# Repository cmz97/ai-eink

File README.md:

# ai-eink

# System 
sudo apt-get install sysstat

# Device Tree Overlay
force_turbo=1
dtoverlay=uart3

# NFC
NFC Driver: https://github.com/2pecshy/eeprom-ST25DV-linux-driver
sudo apt install -y python3-libcamera python3-kms++ libcap-dev

# Drivers
## Camera 
sudo wget https://datasheets.raspberrypi.org/cmio/dt-blob-cam1.bin -O /boot/dt-blob.bin
libcamera-still -q 80 -o test.jpg

For OS Lite 
Open Terminal and enter "sudo nano /boot/config.txt"
Scroll down to the line that reads "camera_auto_detect=1" and change it to "camera_auto_detect=0"
On the next line, enter "dtoverlay=imx219"
Reboot

## Speakers
https://github.com/HinTak/seeed-voicecard
sudo aplay -Dhw:0 test.wav
sudo arecord -D hw:0,0 -f S32_LE -r 16000 -c 2 test.wav
https://www.waveshare.com/wiki/WM8960_Audio_HAT
sudo alsactl store

## Pi-PICO
ampy --port /dev/tty.usbmodem112401 put main.py

## Radxa
sudo apt-get install python3-dev spidev
sudo apt-get update
sudo apt-get install python3-libgpiod

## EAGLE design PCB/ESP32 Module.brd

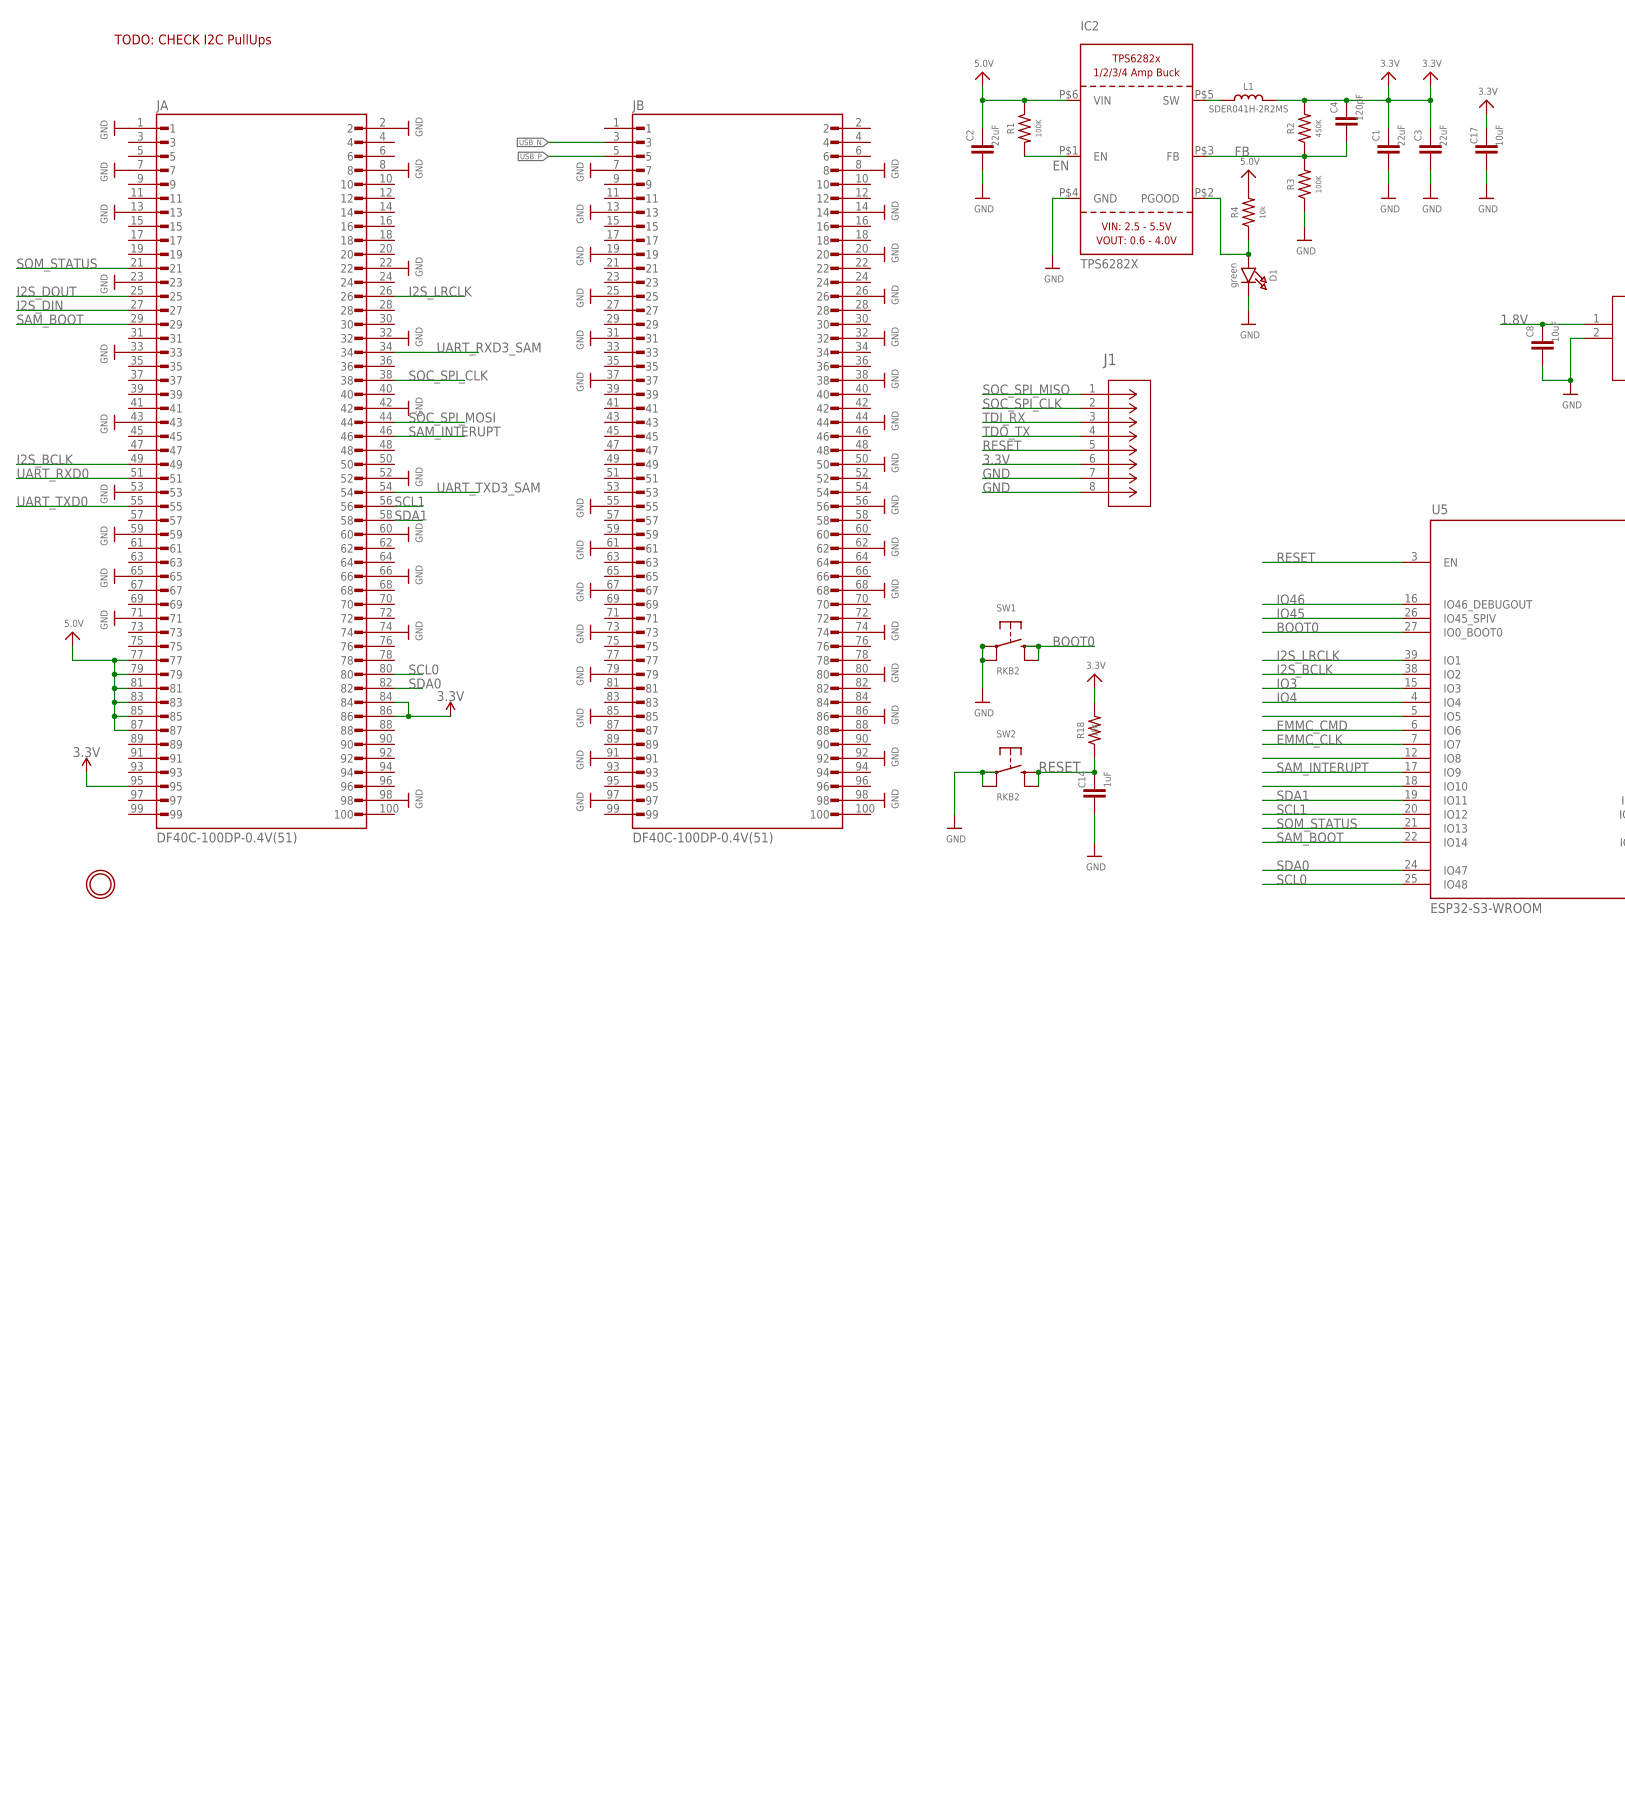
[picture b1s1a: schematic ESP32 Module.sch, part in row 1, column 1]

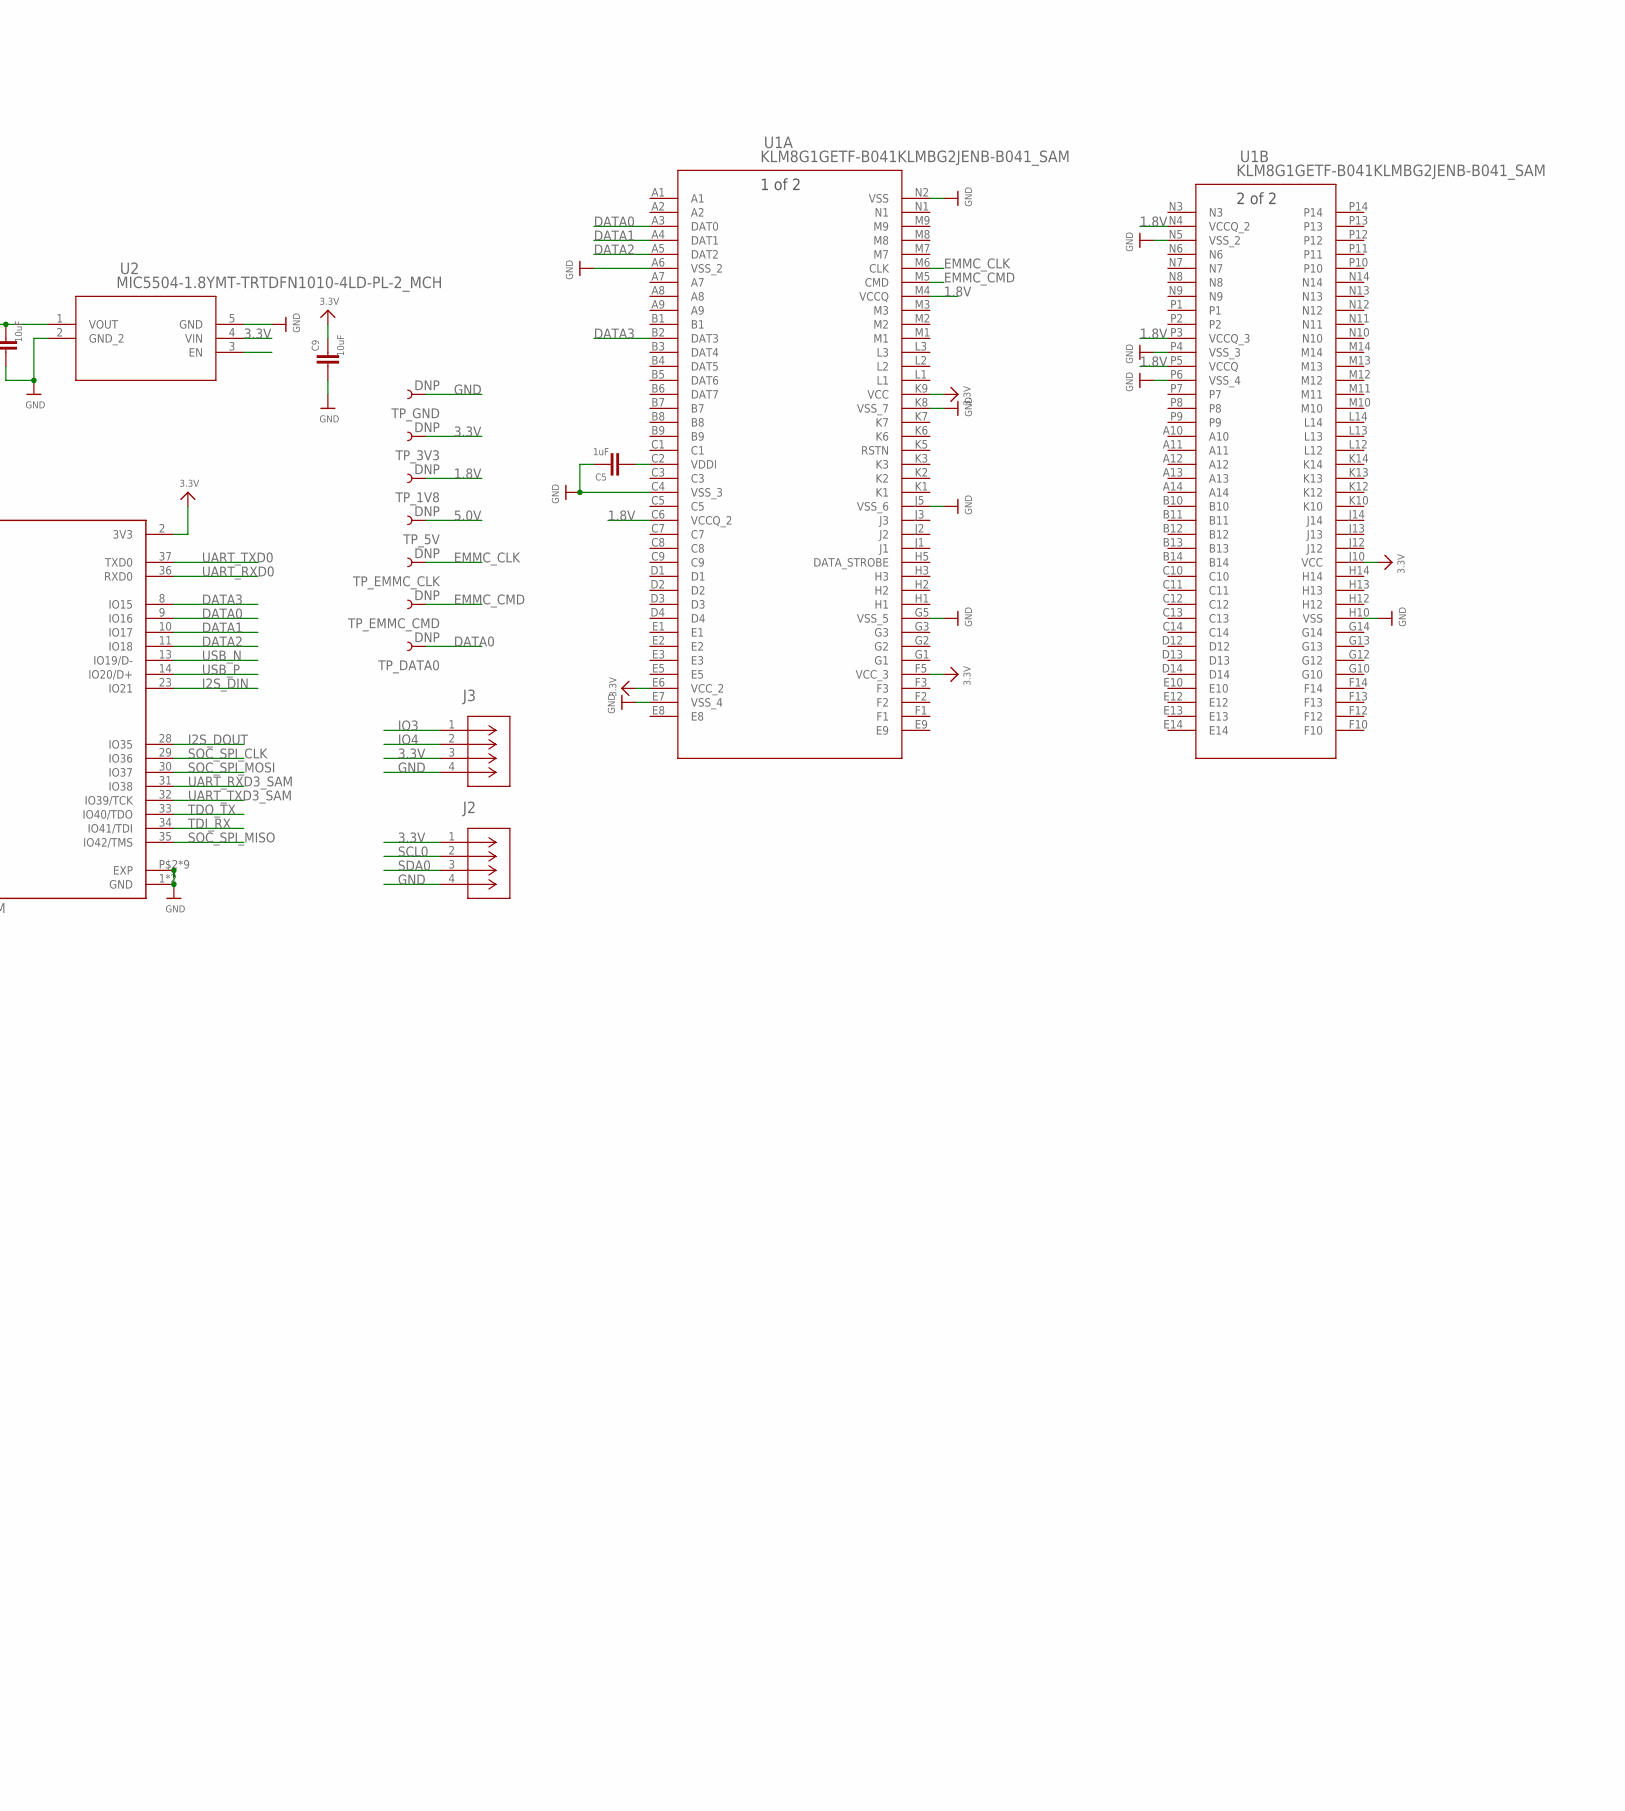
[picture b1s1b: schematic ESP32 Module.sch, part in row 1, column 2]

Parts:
C1, C3: 22uF; CAPC1005X60
C2: 22uF; CAPC1608X85
C4: 120pF; CAPC1005X60
C5, C14: 1uF; CAPC1005X60
C8, C9, C17: 10uF; CAPC1005X60
D1: green; CHIPLED_0603_NOOUTLINE
IC2: TPS6282X; VSON_6
J1: SM08B-SRSS-TB(LF)(SN)CONN_SM08B-SRSS-TB(LF)(SN)_J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; CONN_SM08B-SRSS-TB(LF)(SN)_JST
J2, J3: SM04B-SRSS-TBCONN_SM04B-SRSS-TB_JST; CONN_SM04B-SRSS-TB_JST
JA: DF40C-100DP-0.4V(51); HIROSE_DF40C-100DP-0.4V(51)
JB: DF40C-100DP-0.4V(51); HIROSE_DF40C-100DP-0.4V(51)
L1: SDER041H-2R2MS; INDUCTOR_4X4MM_SRP0415
R1, R3: 100K; RESC1005X40
R2: 450K; RESC1005X40
R4: 10k; RESC1005X40
R18: 10K; RESC1005X40
SW1, SW2: RKB2; BTN_RKB2_4.6X2.8
TP_1V8, TP_3V3, TP_5V: DNP; PAD.03X.03
TP_DATA0: DNP; PAD.03X.03
TP_EMMC_CLK: DNP; PAD.03X.03
TP_EMMC_CMD: DNP; PAD.03X.03
TP_GND: DNP; PAD.03X.03
U1: KLM8G1GETF-B041KLMBG2JENB-B041_SAM; KLMBG2JENB-B041_SAM
U2: MIC5504-1.8YMT-TRTDFN1010-4LD-PL-2_MCH; TDFN1010-4LD-PL-2_MCH
U5: ESP32-S3-WROOM; S3-WROOM32
U$2, U$120: MOUNTINGHOLE2.5; MOUNTINGHOLE_2.5_PLATED

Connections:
1.8V: C8.1, TP_1V8.P$1, U1.C6 (VCCQ_2), U1.M4 (VCCQ), U1.N4 (VCCQ_2), U1.P3 (VCCQ_3), U1.P5 (VCCQ), U2.1 (VOUT)
3.3V: C1.1, C3.1, C4.1, C9.1, C17.1, J1.6, J2.1, J3.3, JA.84, JA.86, JA.95, L1.P$2 (2), R2.2, R18.2, TP_3V3.P$1, U1.E6 (VCC_2), U1.F5 (VCC_3), U1.J10 (VCC), U1.K9 (VCC), U2.4 (VIN), U5.2 (3V3)
5.0V: C2.1, IC2.P$6 (VIN), JA.77, JA.79, JA.81, JA.83, JA.85, JA.87, R1.1, R4.2, TP_5V.P$1
BOOT0: SW1.B (S), SW1.B' (S1), U5.27 (IO0_BOOT0)
DATA0: TP_DATA0.P$1, U1.A3 (DAT0), U5.9 (IO16)
DATA1: U1.A4 (DAT1), U5.10 (IO17)
DATA2: U1.A5 (DAT2), U5.11 (IO18)
DATA3: U1.B2 (DAT3), U5.8 (IO15)
EMMC_CLK: TP_EMMC_CLK.P$1, U1.M6 (CLK), U5.7 (IO7)
EMMC_CMD: TP_EMMC_CMD.P$1, U1.M5 (CMD), U5.6 (IO6)
EN: IC2.P$1 (EN), R1.2
FB: C4.2, IC2.P$3 (FB), R2.1, R3.2
GND: C1.2, C2.2, C3.2, C5.1, C8.2, C9.2, C14.2, C17.2, D1.C, IC2.P$4 (GND), J1.7, J1.8, J2.4, J3.4, JA.1, JA.2, JA.7, JA.8, JA.13, JA.22, JA.23, JA.32, JA.33, JA.42, JA.43, JA.52, JA.53, JA.59, JA.60, JA.65, JA.66, JA.71, JA.74, JA.98, JB.7, JB.8, JB.13, JB.14, JB.19, JB.20, JB.25, JB.26, JB.31, JB.32, JB.37, JB.38, JB.44, JB.50, JB.55, JB.56, JB.61, JB.62, JB.67, JB.68, JB.73, JB.74, JB.79, JB.80, JB.85, JB.86, JB.91, JB.92, JB.97, JB.98, R3.1, SW1.A, SW1.A' (P1), SW2.A, SW2.A' (P1), TP_GND.P$1, U1.A6 (VSS_2), U1.C4 (VSS_3), U1.E7 (VSS_4), U1.G5 (VSS_5), U1.H10 (VSS), U1.J5 (VSS_6), U1.K8 (VSS_7), U1.N2 (VSS), U1.N5 (VSS_2), U1.P4 (VSS_3)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
I2S_BCLK: JA.49, U5.38 (IO2)
I2S_DIN: JA.27, U5.23 (IO21)
I2S_DOUT: JA.25, U5.28 (IO35)
I2S_LRCLK: JA.26, U5.39 (IO1)
IO3: J3.1, U5.15 (IO3)
IO4: J3.2, U5.4 (IO4)
IO10: U5.18 (IO10)
IO45: U5.26 (IO45_SPIV)
IO46: U5.16 (IO46_DEBUGOUT)
unnamed: IC2.P$5 (SW), L1.P$1 (1)
unnamed: D1.A, IC2.P$2 (PGOOD), R4.1
unnamed: C5.2, U1.C2 (VDDI)
RESET: C14.1, J1.5, R18.1, SW2.B (S), SW2.B' (S1), U5.3 (EN)
SAM_BOOT: JA.29, U5.22 (IO14)
SAM_INTERUPT: JA.46, U5.17 (IO9)
SCL0: J2.2, JA.80, U5.25 (IO48)
SCL1: JA.56, U5.20 (IO12)
SDA0: J2.3, JA.82, U5.24 (IO47)
SDA1: JA.58, U5.19 (IO11)
SOC_SPI_CLK: J1.2, JA.38, U5.29 (IO36)
SOC_SPI_MISO: J1.1, U5.35 (IO42/TMS)
SOC_SPI_MOSI: JA.44, U5.30 (IO37)
SOM_STATUS: JA.21, U5.21 (IO13)
TDI_RX: J1.3, U5.34 (IO41/TDI)
TDO_TX: J1.4, U5.33 (IO40/TDO)
UART_RXD0: JA.51, U5.36 (RXD0)
UART_RXD3_SAM: JA.34, U5.31 (IO38)
UART_TXD0: JA.55, U5.37 (TXD0)
UART_TXD3_SAM: JA.54, U5.32 (IO39/TCK)
USB_N: JB.3, U5.13 (IO19/D-)
USB_P: JB.5, U5.14 (IO20/D+)

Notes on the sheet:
TODO: CHECK I2C PullUps

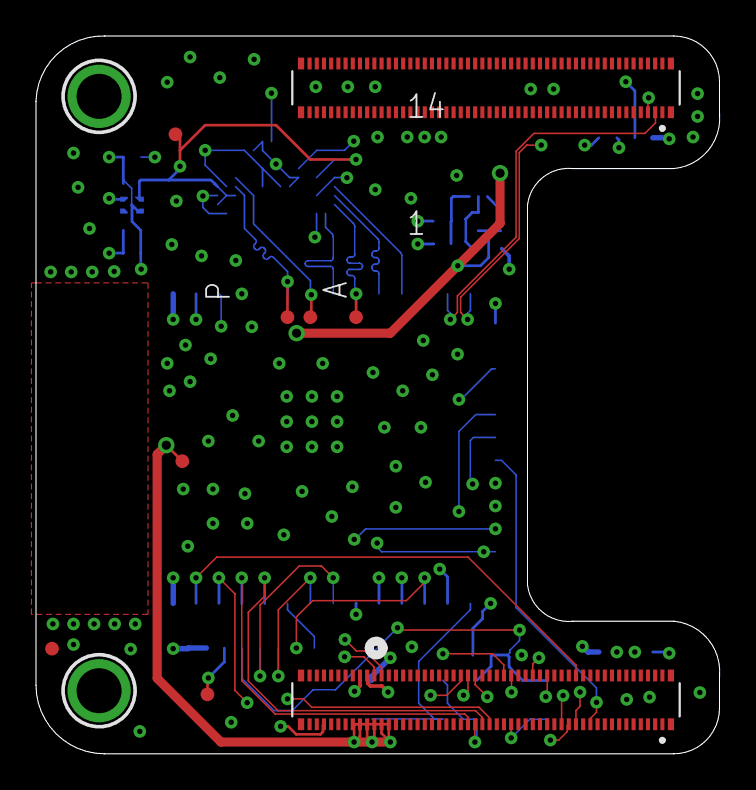
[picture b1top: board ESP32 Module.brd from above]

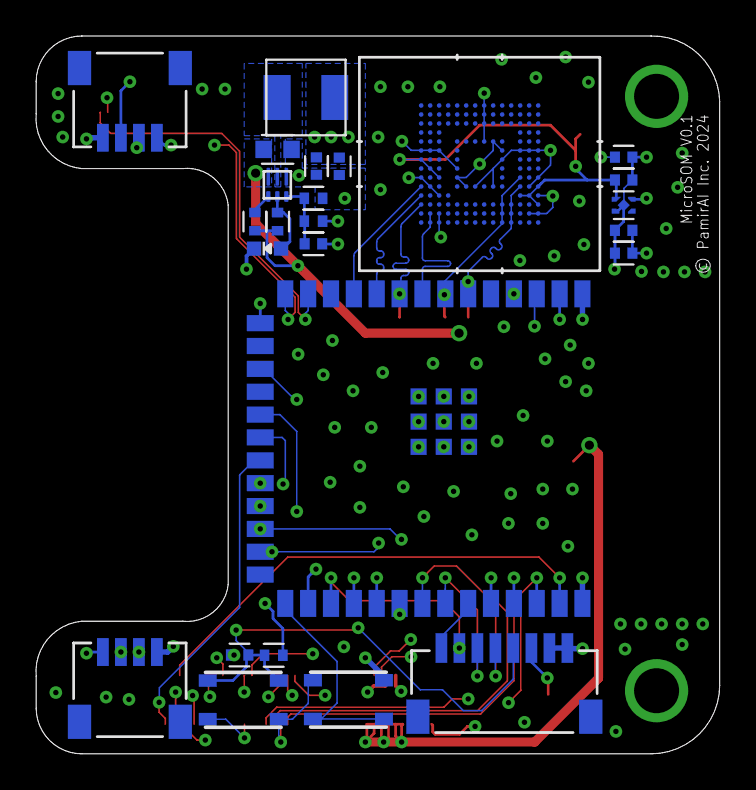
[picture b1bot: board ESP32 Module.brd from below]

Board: 4 copper layers, 38.0 x 39.9 mm, 36 parts (25 on the bottom side), 41 nets.

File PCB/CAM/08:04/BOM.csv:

Comment,Designator,Footprint,LCSC Part #
1uF,C5 C14,CAPC1005X60,
10K,R18,RESC1005X40,
10k,R4,RESC1005X40,
10uF,C8 C9 C17,CAPC1005X60,
22uF,C1,CAPC1005X60,
22uF,C2,CAPC1608X85,
22uF,C3,CAPC1005X60,
100K,R1 R3,RESC1005X40,
120pF,C4,CAPC1005X60,
450K,R2,RESC1005X40,
ESP32-S3-WROOM,U5,S3-WROOM32,
KLM8G1GETF-B041KLMBG2JENB-B041_SAM,U1,KLMBG2JENB-B041_SAM,
MIC5504-1.8YMT-TRTDFN1010-4LD-PL-2_MCH,U2,TDFN1010-4LD-PL-2_MCH,
RKB2,SW1 SW2,BTN_RKB2_4.6X2.8,
SDER041H-2R2MS,L1,INDUCTOR_4X4MM_SRP0415,
SM04B-SRSS-TBCONN_SM04B-SRSS-TB_JST,J2 J3,CONN_SM04B-SRSS-TB_JST,
SM08B-SRSS-TB(LF)(SN)CONN_SM08B-SRSS-TB(LF)(SN)_JST,J1,CONN_SM08B-SRSS-TB(LF)(SN)_JST,
TPS6282X,IC2,VSON_6,
green,D1,CHIPLED_0603_NOOUTLINE,
DF40C-100DP-0.4V(51),JA JB,HIROSE_DF40C-100DP-0.4V(51),
DNP,TP_1V8 TP_3V3 TP_5V TP_DATA0 TP_EMMC_CLK TP_EMMC_CMD TP_GND,PAD.03X.03,

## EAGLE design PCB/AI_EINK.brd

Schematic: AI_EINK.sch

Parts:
BUD: EVQ-P7A01P; SW_EVQ-P7A01P
BUP: EVQ-P7A01P; SW_EVQ-P7A01P
BUS: EVQ-P7A01P; SW_EVQ-P7A01P
C1, C3, C7, C21, C22, C23, C26, C28, C32, C33, C36, C40, C45, C46, C53, C59, C60, C61, C62, C65, C68, C79, C80: 10uF; CAPC1005X60
C2: 2.2uF; CAPC1005X60
C4, C24, C31, C43, C44, C47, C48, C49, C50, C58, C67, C69, C71, C72, C73, C74, C77: 0.1uF; CAPC1005X60
C5, C8, C9, C10, C11, C12, C13, C14, C15, C16, C34, C35: 1uF; CAPC1005X60
C6, C25: 100uF; C1210
C17: 4.7uF/50V; CAPC1005X60
C18: 4.7uF; CAPC1608X85
C19, C30, C75, C76: 1.0uF; CAPC1005X60
C20: 0.47uF; CAPC1005X60
C27: 27pF; CAPC1005X60
C29: 4.7uF; CAPC1005X60
C42: 0.1uF; CAPC1608X85
C63, C64: 100pF; CAPC1005X60
C66: 2.2uF+; CAPC1005X60
C82, C83: 15p; CAPC1005X60
C2040: RP2040TR13QFN56_7X7_RPI; QFN56_7X7_RPI
CAMERA: C262642; CON_524372271_MOL
D1: ACT (MHT192JGCT); LED-0603@1
D2, D3, D4: MBR0530; SOD3716X135N
D5: CHARGING FC-1608B1-470; LED-0603
D6, D7: PMIC; LED-0603
EINK_524352471: 524372471; CON_524372471_MOL
FB1, FB2, FB3, FB5: FERRITE_BEAD; BEADC1608X95N
GND, GND7, GND13, GND22, GND26, GND27, GND34, GND36, GND37, GND40, GND41, GND42: DNP; PAD.03X.03
H2: BM04B-SRSS-TBCONN4_BM04B-SRSS_JST; CONN4_BM04B-SRSS_JST
IC1: LIS3MDL; LGA12_2X2MM
IC3: WM8960; QFN32_5MM
J1: SM03B-SRSS-TBCONN_SM03B-SRSS-TB_JST; CONN_SM03B-SRSS-TB_JST
J2: C393939; USB-C-16P
J4, J5: BM04B-SRSS-TBCONN4_BM04B-SRSS_JST; CONN4_BM04B-SRSS_JST
J6: SM04B-SRSS-TBCONN_SM04B-SRSS-TB_JST; CONN_SM04B-SRSS-TB_JST
L1: 6.8uH C36410; INDUCTOR_5X5MM_TDK_VLC5045
L3: FNR5012S100MT 10uH; IND_LQH5BPN2R2NT0L
LED2: LED_RED; LEDC1608X65N_RND-R
LED3: SYS_POW (19-213/Y2C-CQ2R2L/3T(CY)); LED-0603
LOW_BATT: LED_RED; LEDC1608X65N_RND-R
LS1: CMS-18138A-SP; CUI_CMS-18138A-SP
M.2KEYM(NGFF): 1-2199119-5 OR C841645; TE_1-2199119-5
OSC2: ECS-3225MV; OSC_3.2X2.5MM
Q1: SI1308EDL-T1-GE3; SOT65P210X110-3N
Q2: DMG2307L; SOT96P240X110-3N
Q3, Q4: NMOS_C7465427; SOT23
R1: 1.87M (TPA2005D1DRBR); RESC1005X40
R2: 340K (RTT053403FTP); RESC1005X40
R3: 1.87M; RESC1005X40
R4, R13, R36: 200K; RESC1005X40
R5, R14, R20, R23: 1K; RESC1005X40
R6: 590; RESC1005X40
R7: 1.1k; RESC1005X40
R8, R10, R34, R35: 1k; RESC1005X40
R9: 0.47; RESC1005X40
R11, R33, R43: 10K; RESC1005X40
R12: 0.01; 1206
R15, R18, R25, R26, R40, R42: 4.7K; RESC1005X40
R16, R17, R27, R28, R37, R39: 10k; RESC1005X40
R19: 5.1K; RESC1005X40
R21: 5.1k; RESC1005X40
R22: 180; RESC1005X40
R24: 100k; RESC1005X40
R30: 36k; RESC1005X40
R31, R32: 27; RESC1005X40
R38: 4.7k; RESC1005X40
R41: 47K; RESC1005X40
R44: 6.57k; RESC1005X40
RPI-CM1: DF40C-100DS-0.4V(51); RPI-CM4
RPIBOOT, RPIBOOT1, RPIBOOT2, RPIBOOT3, RPIBOOT4, RPIBOOT6, RPIBOOT8, RPIBOOT9, RPIBOOT10, RPIBOOT11, RPIBOOT12: DNP; PAD.03X.03
RPIBOOT5, RPIBOOT7: TEST-POINT3; PAD.03X.03
SJ1, SJ6: DNP; PAD-JUMPER-2-NC_BY_TRACE_YES_SILK
T1: MMUN2133LT1G; SC59-BEC
U1: TPS61092RSAR; PVQFN-16
U2: MC74VHC1G14DFT1G; SOT65P210X110-5N
U3: BQ27441DRZR-G1A; PDSO-N12
U4: BQ24075; PVQFN-N16
U5: MC74VHC1G14DFT1G OR C66196; SOT65P210X110-5N
U6: LSM6DS3; LGA-14L
U7: SN74LVC244ARWPRRWP0020A; RWP0020A
U9: EMC2301-1-ACZL-TRMSOP8_MC_MCH-L; MSOP8_MC_MCH-L
U10, U11, U15: AP2112-3.3K; SOT23-5
U12: C233266; XDCR_SPU0410LR5H-QB
U13: TPD4EUSB30DQARDQA10; DQA10
U14: OPA344; SOT23-5
U16: W25Q16JVUXIQ_TR; PSON50P300X200X60-9N
U17, U18, U19, U20, U21, U22, U23, U24: TPD1E1B04DPYRDPY2_TEX; DPY2_TEX
U25: DRV2605LDGSR; SOP50P490X110-10N
USB2.0MUX: TS3USB30RSWR; 10-UFQFN
USB_BOOT_N: DNP; PAD.03X.03
Y1: ABM8-272-T3; ABM8272T3

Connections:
1V8BQ: C20.1, U3.5 (VDD)
2A3: U7.14 (2A3)
2A4: U7.16 (2A4)
2Y3: U7.4 (2Y3)
2Y4: U7.2 (2Y4)
3.3V: C28.1, C36.2, C49.1, CAMERA.22, D1.A, IC1.5 (VDD), IC1.6 (VDDIO), IC3.8 (DCVDD), IC3.10 (DBVDD), OSC2.1 (INH), OSC2.4 (VCC), R15.2, R18.2, R30.2, R33.2, RPI-CM1.84 (CM4_3.3V(OUTPUT)), RPI-CM1.86 (CM4_3.3V(OUTPUT)), RPIBOOT2.P$1, SJ6.1, U2.5 (VCC), U6.5 (VDDIO), U6.8 (VDD), U9.3 (VDD)
3V3_EINK: C9.1, C17.1, EINK_524352471.9, EINK_524352471.10, L3.1, Q2.3 (D)
5.0V: C2.1, C6.1, C25.1, C42.1, C59.1, C60.1, C61.1, C65.1, C66.1, IC3.21 (SPKVDD2), IC3.26 (SPKVDD1), J6.3, R3.2, R5.1, RPI-CM1.77 (+5V(INPUT)), RPI-CM1.79 (+5V(INPUT)), RPI-CM1.81 (+5V(INPUT)), RPI-CM1.83 (+5V(INPUT)), RPI-CM1.85 (+5V(INPUT)), RPI-CM1.87 (+5V(INPUT)), RPIBOOT1.P$1, U1.1 (VOUT), U1.15 (VOUT), U1.16 (VOUT), U10.1 (IN), U10.3 (EN)
!CE!: R24.1, U4.4 (!CE!)
!CHG!: R22.2, U4.9 (!CHG!)
AGND: C67.2, C68.2, FB5.2, IC3.28 (AGND), IC3.33 (AGND)
AUDIO_MCLK: IC3.11 (MCLK), OSC2.3 (OUT)
AVDD: C50.1, C58.1, C67.1, C68.1, FB1.2, IC3.32 (AVDD), R27.2, U12.4 (VDD), U14.5 (P$V+)
BATTERY_IN: C19.1, J1.3, R12.2, U3.6 (BAT), U3.8 (SRP)
BOOST_EN: Q3.3 (D), R13.1, R36.2
BUTTON_D: BUD.2_1 (2), BUD.2_2 (2), C2040.29 (GPIO18)
BUTTON_S: BUS.2_1 (2), BUS.2_2 (2), C2040.27 (GPIO16)
BUTTON_U: BUP.2_1 (2), BUP.2_2 (2), C2040.28 (GPIO17)
CAM0_C_N: RPI-CM1.140 (CAM0_C_N)
CAM0_C_P: RPI-CM1.142 (CAM0_C_P)
CAM0_D0_N: RPI-CM1.128 (CAM0_D0_N)
CAM0_D0_P: RPI-CM1.130 (CAM0_D0_P)
CAM0_D1_N: RPI-CM1.134 (CAM0_D1_N)
CAM0_D1_P: RPI-CM1.136 (CAM0_D1_P)
CAM1_C_N: CAMERA.8, RPI-CM1.127 (CAM1_C_N)
CAM1_C_P: CAMERA.9, RPI-CM1.129 (CAM1_C_P)
CAM1_D0_N: CAMERA.2, RPI-CM1.115 (CAM1_D0_N)
CAM1_D0_P: CAMERA.3, RPI-CM1.117 (CAM1_D0_P)
CAM1_D1_N: CAMERA.5, RPI-CM1.121 (CAM1_D1_N)
CAM1_D1_P: CAMERA.6, RPI-CM1.123 (CAM1_D1_P)
CAM1_D2_N: CAMERA.11, RPI-CM1.133 (CAM1_D2_N)
CAM1_D2_P: CAMERA.12, RPI-CM1.135 (CAM1_D2_P)
CAM1_D3_N: CAMERA.14, RPI-CM1.139 (CAM1_D3_N)
CAM1_D3_P: CAMERA.15, RPI-CM1.141 (CAM1_D3_P)
CAM_GPIO: CAMERA.17, RPI-CM1.97 (CAMERA_GPIO)
CDD: C10.1, EINK_524352471.7
DSI0_C_N: RPI-CM1.169 (DSI0_C_N)
DSI0_C_P: RPI-CM1.171 (DSI0_C_P)
DSI0_D0_N: RPI-CM1.157 (DSI0_D0_N)
DSI0_D0_P: RPI-CM1.159 (DSI0_D0_P)
DSI0_D1_N: RPI-CM1.163 (DSI0_D1_N)
DSI0_D1_P: RPI-CM1.165 (DSI0_D1_P)
DSI1_C_N: RPI-CM1.187 (DSI1_C_N)
DSI1_C_P: RPI-CM1.189 (DSI1_C_P)
DSI1_D0_N: RPI-CM1.175 (DSI1_D0_N)
DSI1_D0_P: RPI-CM1.177 (DSI1_D0_P)
DSI1_D1_N: RPI-CM1.181 (DSI1_D1_N)
DSI1_D1_P: RPI-CM1.183 (DSI1_D1_P)
DSI1_D2_N: RPI-CM1.193 (DSI1_D2_N)
DSI1_D2_P: RPI-CM1.195 (DSI1_D2_P)
DSI1_D3_N: RPI-CM1.194 (DSI1_D3_N)
DSI1_D3_P: RPI-CM1.196 (DSI1_D3_P)
EINK_BUSY: C2040.13 (GPIO10), EINK_524352471.16, RPIBOOT9.P$1, U7.1 (1A1), U18.2 (I/O)
EINK_CS: C2040.16 (GPIO13), EINK_524352471.13, GND41.P$1, U7.11 (1Y4), U20.2 (I/O)
EINK_D/C: C2040.15 (GPIO12), EINK_524352471.14, RPIBOOT10.P$1, U7.13 (1Y3), U19.2 (I/O)
EINK_RESET: C2040.14 (GPIO11), EINK_524352471.15, GND40.P$1, U7.15 (1Y2), U17.2 (I/O)
ENABLE: R13.2, U1.11 (EN)
EXT_VCC_PCIE: M.2KEYM(NGFF).2, M.2KEYM(NGFF).4, M.2KEYM(NGFF).12, M.2KEYM(NGFF).14, M.2KEYM(NGFF).16, M.2KEYM(NGFF).18, M.2KEYM(NGFF).70, M.2KEYM(NGFF).72, M.2KEYM(NGFF).74, RPIBOOT3.P$1
FAN_PWM: J6.1, U9.5 (PWM)
GDR: EINK_524352471.23, Q1.1 (G), R11.2
GND: C1.2, C2.2, C3.2, C4.2, C5.2, C6.2, C7.2, C8.2, C9.2, C10.2, C11.2, C12.2, C13.2, C14.2, C15.2, C16.2, C17.2, C19.2, C20.2, C21.2, C22.2, C23.2, C24.1, C25.2, C26.2, C28.2, C30.2, C31.2, C32.2, C33.2, C34.1, C35.2, C36.1, C40.2, C42.2, C43.2, C44.2, C45.2, C46.2, C47.2, C48.2, C49.2, C50.2, C53.2, C58.2, C59.2, C60.2, C61.2, C62.2, C63.2, C64.2, C65.2, C66.2, C69.2, C71.2, C72.2, C73.2, C74.2, C75.2, C76.2, C77.2, C79.2, C80.2, C82.2, C83.1, C2040.19 (TESTEN), C2040.57 (GND), CAMERA.1, CAMERA.4, CAMERA.7, CAMERA.10, CAMERA.13, CAMERA.16, CAMERA.19, CAMERA.P1, CAMERA.P2, D2.1 (K), EINK_524352471.8, EINK_524352471.17, EINK_524352471.P1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
GND_2: U13.3 (GND_2)
GPOUT: R33.1, U3.12 (GPOUT)
HAP_3V3: C33.1, C35.1, U15.5 (OUT), U25.5 (EN), U25.6 (VDD/NC), U25.10 (VDD)
HDMI0_CEC: RPI-CM1.151 (HDMI0_CEC)
HDMI0_CLK_N: RPI-CM1.190 (HDMI0_CLK_N)
HDMI0_CLK_P: RPI-CM1.188 (HDMI0_CLK_P)
HDMI0_HOTPLUG: RPI-CM1.153 (HDMI0_HOTPLUG)
HDMI0_SCL: RPI-CM1.200 (HDMI0_SCL)
HDMI0_SDA: RPI-CM1.199 (HDMI0_SDA)
HDMI0_TX0_N: RPI-CM1.184 (HDMI0_TX0_N)
HDMI0_TX0_P: RPI-CM1.182 (HDMI0_TX0_P)
HDMI0_TX1_N: RPI-CM1.178 (HDMI0_TX1_N)
HDMI0_TX1_P: RPI-CM1.176 (HDMI0_TX1_P)
HDMI0_TX2_N: RPI-CM1.172 (HDMI0_TX2_N)
HDMI0_TX2_P: RPI-CM1.170 (HDMI0_TX2_P)
HDMI1_CEC: RPI-CM1.149 (HDMI1_CEC)
HDMI1_CLK_N: RPI-CM1.166 (HDMI1_CLK_N)
HDMI1_CLK_P: RPI-CM1.164 (HDMI1_CLK_P)
HDMI1_HOTPLUG: RPI-CM1.143 (HDMI1_HOTPLUG)
HDMI1_SCL: RPI-CM1.147 (HDMI1_SCL)
HDMI1_SDA: RPI-CM1.145 (HDMI1_SDA)
HDMI1_TX0_N: RPI-CM1.160 (HDMI1_TX0_N)
HDMI1_TX0_P: RPI-CM1.158 (HDMI1_TX0_P)
HDMI1_TX1_N: RPI-CM1.154 (HDMI1_TX1_N)
HDMI1_TX1_P: RPI-CM1.152 (HDMI1_TX1_P)
HDMI1_TX2_N: RPI-CM1.148 (HDMI1_TX2_N)
HDMI1_TX2_P: RPI-CM1.146 (HDMI1_TX2_P)
I2S_BCLK: IC3.12 (BCLK), RPI-CM1.49 (GPIO18)
I2S_DIN: IC3.16 (ADCDAT), RPI-CM1.27 (GPIO20)
I2S_DOUT: IC3.14 (DACDAT), RPI-CM1.25 (GPIO21)
I2S_LRCLK: IC3.13 (DACLRC), IC3.15 (ADCLRC/GPIO1), RPI-CM1.26 (GPIO19)
ILIM: R7.1, U4.12 (ILIM)
ISET: R6.1, U4.16 (ISET)
LBO: T1.B, U1.12 (LBO)
LEFT_N: C64.1, FB3.2, LS1.N
LEFT_P: C63.1, FB2.2, LS1.P
MICBIAS: C46.1, C48.1, IC3.1 (MICBIAS)
unnamed: L1.P$2 (2), U1.3 (SW), U1.4 (SW)
unnamed: LOW_BATT.A, R20.1
unnamed: R1.1, R2.2, U1.9 (LBI)
unnamed: LED2.A, R5.2
unnamed: R3.1, R4.2, U1.14 (FB)
unnamed: R20.2, T1.C
unnamed: RPI-CM1.78 (GPIO_VREF), SJ6.2
unnamed: C31.1, IC1.4 (C1)
unnamed: RPI-CM1.95 (PI_LED_!PWR), U2.2 (IN_A)
unnamed: C29.1, U12.1 (OUTPUT)
unnamed: R8.2, U2.4 (OUT_~Y)
unnamed: LED3.A, R8.1
unnamed: C27.1, R38.1, R39.2, U14.4 (-IN)
unnamed: R10.2, RPI-CM1.21 (PI_!LED_ACTIVITY)
unnamed: D1.C, R10.1
unnamed: C34.2, U25.1 (REG)
unnamed: D5.C, R22.1
unnamed: D7.C, R14.1
unnamed: C18.1, D2.2 (A), D3.1 (K)
unnamed: C29.2, R38.2
unnamed: D6.C, R23.1
unnamed: C30.1, R27.1, R37.2, U14.3 (+IN)
unnamed: C18.2, D4.2 (A), L3.2, Q1.3 (D)
unnamed: Q4.3 (D), R34.2, USB_BOOT_N.P$1
unnamed: C83.2, R35.2, Y1.3 (CRYSTAL_2)
unnamed: J2.B5 (CC2), R21.2
unnamed: Q2.1 (G), R43.2, R44.1
unnamed: R44.2, U5.4 (OUT_~Y)
unnamed: J2.A5 (CC1), R19.2
unnamed: FB2.1, IC3.25 (SPK_LP)
unnamed: FB3.1, IC3.23 (SPK_LN)
NC: EINK_524352471.24
N_RPIBOOT: RPI-CM1.93 (!RPIBOOT), RPIBOOT.P$1
OUT: C62.1, C69.1, FB1.1, U10.5 (OUT)
PCIE_!RST: M.2KEYM(NGFF).50, RPI-CM1.109 (PCIE_!RST)
PCIE_CLK_!REQ: M.2KEYM(NGFF).52, RPI-CM1.102 (PCIE_CLK_!REQ)
PCIE_CLK_N: M.2KEYM(NGFF).53, RPI-CM1.112 (PCIE_CLK_N)
PCIE_CLK_P: M.2KEYM(NGFF).55, RPI-CM1.110 (PCIE_CLK_P)
PCIE_RX_N: M.2KEYM(NGFF).41, RPI-CM1.118 (PCIE_RX_N)
PCIE_RX_P: M.2KEYM(NGFF).43, RPI-CM1.116 (PCIE_RX_P)
PCIE_TX_N: M.2KEYM(NGFF).47, RPI-CM1.124 (PCIE_TX_N)
PCIE_TX_P: M.2KEYM(NGFF).49, RPI-CM1.122 (PCIE_TX_P)
PI_1V8: RPI-CM1.88 (CM4_1.8V(OUTPUT)), RPI-CM1.90 (CM4_1.8V(OUTPUT))
PREVGH: C16.1, D4.1 (K), EINK_524352471.4
PREVGL: C14.1, D3.2 (A), EINK_524352471.2
RESE: EINK_524352471.22, Q1.2 (S), R9.2
RESERVED@104: RPI-CM1.104 (RESERVED)
RESERVED@106: RPI-CM1.106 (RESERVED)
RINPUT1: C27.2, IC3.5 (RINPUT1), R39.1, U14.1 (OUT)
SAM_1V1: C76.1, C77.1, C2040.23 (DVDD_2), C2040.45 (VREG_VOUT), C2040.50 (DVDD)
SAM_3V3: BUD.1_1 (1), BUD.1_2 (1), BUP.1_1 (1), BUP.1_2 (1), BUS.1_1 (1), BUS.1_2 (1), C7.1, C24.2, C43.1, C44.1, C71.1, C72.1, C73.1, C74.1, C75.1, C80.1, C2040.1 (IOVDD_2), C2040.10 (IOVDD_3), C2040.22 (IOVDD_4), C2040.33 (IOVDD_5), C2040.42 (IOVDD_6), C2040.43 (ADC_AVDD), C2040.44 (VREG_VIN), C2040.48 (USB_VDD), C2040.49 (IOVDD), D7.A, J4.1, Q2.2 (S), R16.2, R17.2, R25.2, R26.2, R28.2, R40.2, R42.2, R43.1, U5.5 (VCC), U7.19 (VCC), U11.5 (OUT), U16.8 (VCC), USB2.0MUX.9 (VCC)
SAM_BOOT: Q4.1 (G), RPI-CM1.29 (GPIO16)
SAM_EINK_PWR: C2040.12 (GPIO9), U5.2 (IN_A)
SAM_EINK_SWITCH: C2040.34 (GPIO22), U7.18 (2OE_N), U7.20 (1OE_N)
SAM_GPIO3: C2040.5 (GPIO3)
SAM_GPIO4: C2040.6 (GPIO4)
SAM_GPIO5: C2040.7 (GPIO5)
SAM_GPIO6: C2040.8 (GPIO6)
SAM_GPIO7: C2040.9 (GPIO7)
SAM_GPIO8: C2040.11 (GPIO8)
SAM_GPIO23: C2040.35 (GPIO23)
SAM_GPIO26/ADC0: C2040.38 (GPIO26/ADC0)
SAM_GPIO27/ADC1: C2040.39 (GPIO27/ADC1)
SAM_GPIO28/ADC2: C2040.40 (GPIO28/ADC2)
SAM_GPIO29/ADC3: C2040.41 (GPIO29/ADC3)
SAM_INTERUPT: C2040.4 (GPIO2), RPI-CM1.46 (GPIO22), RPIBOOT12.P$1
SAM_QSPI_SCLK: C2040.52 (QSPI_SCLK), U16.6 (CLK)
SAM_QSPI_SCN: C2040.56 (QSPI_SCN), R34.1, U16.1 (!CS!)
SAM_QSPI_SD0: C2040.53 (QSPI_SD0), U16.5 (IO0)
SAM_QSPI_SD1: C2040.55 (QSPI_SD1), U16.2 (IO1)
SAM_QSPI_SD2: C2040.54 (QSPI_SD2), U16.3 (IO2)
SAM_QSPI_SD3: C2040.51 (QSPI_SD3), U16.7 (IO3)
SAM_RUN: C2040.26 (RUN)
SAM_SCL: C2040.37 (GPIO25), J4.3, R26.1, RPIBOOT8.P$1, U3.2 (SCL), U25.2 (SCL)
SAM_SDA: C2040.36 (GPIO24), GND37.P$1, J4.2, R25.1, U3.1 (SDA), U25.3 (SDA)
SAM_SWCLK: C2040.24 (SWCLK)
SAM_SWD: C2040.25 (SWD)
SAM_USB_DM: C2040.46 (USB_DM), R32.2
SAM_USB_DP: C2040.47 (USB_DP), R31.2
SAM_USB_SWITCH: C2040.30 (GPIO19), R41.1, USB2.0MUX.8 (~OE)
SAM_XIN: C82.1, C2040.20 (XIN), Y1.1 (CRYSTAL_1)
SAM_XOUT: C2040.21 (XOUT), R35.1
SCL0: CAMERA.20, RPI-CM1.80 (SCL0)
SCL1: IC1.1 (SCL), IC3.17 (SCL), R18.1, RPI-CM1.56 (GPIO3), RPIBOOT6.P$1, U6.13 (SCL), U9.2 (SMCLK)
SDA0: CAMERA.21, RPI-CM1.82 (SDA0)
SDA1: GND7.P$1, IC1.11 (SDA), IC3.18 (SDA), R15.1, RPI-CM1.58 (GPIO2), U6.14 (SDA), U9.1 (SMDATA)
SOC_EINK_BUSY: RPI-CM1.40 (GPIO9), U7.17 (1Y1)
SOC_EINK_CS: RPI-CM1.39 (GPIO8), U7.7 (1A4)
SOC_EINK_D/C: RPI-CM1.30 (GPIO6), U7.5 (1A3)
SOC_EINK_RESET: RPI-CM1.28 (GPIO13), U7.3 (1A2)
SOC_SPI_CLK: RPI-CM1.38 (GPIO11), U7.10 (2A1)
SOC_SPI_MOSI: RPI-CM1.44 (GPIO10), U7.12 (2A2)
SPI_CLK: C2040.17 (GPIO14), EINK_524352471.12, RPIBOOT11.P$1, U7.8 (2Y1), U21.2 (I/O)
SPI_MOSI: C2040.18 (GPIO15), EINK_524352471.11, GND42.P$1, U7.6 (2Y2), U22.2 (I/O)
SYS_PI_ON: C2040.32 (GPIO21), Q3.1 (G)
TACH: J6.2, R30.1, U9.6 (TACH)
THERM: J1.2, SJ1.1
TS: SJ1.2, U3.10 (BIN), U4.1 (TS)
TSCL: EINK_524352471.19, U23.2 (I/O)
TSDA: EINK_524352471.18, U24.2 (I/O)
U25_OUT+: H2.1, H2.2, U25.7 (OUT+)
U25_OUT-: H2.3, H2.4, U25.9 (OUT-)
UART_RXD0: J5.2, RPI-CM1.51 (GPIO15)
UART_RXD3_SAM: C2040.2 (GPIO0), R40.1, RPI-CM1.34 (GPIO5), RPIBOOT7.P$1
UART_TXD0: J5.1, RPI-CM1.55 (GPIO14)
UART_TXD3_SAM: C2040.3 (GPIO1), GND36.P$1, R42.1, RPI-CM1.54 (GPIO4)
USB_N: J2.A7 (D-), J2.B7 (D-), RPI-CM1.103 (USB_N), U13.5 (D2-), USB2.0MUX.5 (D-)
USB_OTG_ID: RPI-CM1.101 (USB_OTG_ID)
USB_P: J2.A6 (D+), J2.B6 (D+), RPI-CM1.105 (USB_P), U13.4 (D2+), USB2.0MUX.3 (D+)
USB_SAM_N: R32.1, USB2.0MUX.7 (D1-)
USB_SAM_P: R31.1, USB2.0MUX.1 (D1+)
VBUS: C3.1, C22.1, C53.1, J2.VBUS1 (VBUS), J2.VBUS2 (VBUS), U4.13 (IN)
VCOM: C15.1, EINK_524352471.1
VDAC_COMP: RPI-CM1.111 (VDAC_COMP)
VGH: C8.1, EINK_524352471.20
VGL: C5.1, EINK_524352471.21
VMID: C45.1, C47.1, IC3.27 (VMID)
VOUT: C1.1, C4.1, C21.1, C26.1, C32.1, C79.1, D5.A, D6.A, L1.P$1 (1), R1.2, R36.1, RPIBOOT4.P$1, T1.E, U1.8 (VBAT), U4.5 (EN2), U4.10 (OUT), U4.11 (OUT), U11.1 (IN), U11.3 (EN), U15.1 (IN), U15.3 (EN)
VPP: C11.1, EINK_524352471.6
VSH: C12.1, EINK_524352471.5
VSL: C13.1, EINK_524352471.3
V_BATT: C23.1, C40.1, R12.1, RPIBOOT5.P$1, U3.7 (SRN), U4.2 (BAT), U4.3 (BAT)

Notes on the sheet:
Both grounds must be connected on the PCB at only one point close to the GND pin.
See Pg 15 1st para
6.8uH power w/2A current
R3 = 1.9Mohm for 5.2V R3 = 1.1Mohm for 3.3V
Sets fast charge current - R_ISET range: 590-8.9k - I_CHG = ~885 / R_ISET - EX: R_ISET = 590 : I_CHG = 1.5A
Sets combined system load and battery charge currents pulled from USB input. - I_INMAX=1650 / R_ILIM - R_ILIM range: 1.1k-8k - EX: R_ILIM = 1.1k : I_INMAX = 1.5A
BQ24075 - 1.5A USB-Friendly LiPo Battery Charger & Power-Path Management
BQ27441-G1 Fuel Gauge
SJ1: Cut to disable TS bypass.
SJ3: Cut to set custom ISET.
SJ4: Cut to set custom ILIM.
ILIM - System/Load Current Limit
ISET-Charge Current
TMR - Saftey Timers
Sets pre-charge and fast-charge safety timers. - Leave unconnected to set default (30min pre, 5hr charge time) - Connect to GND to disable - R_TMR range: 18k-72k - T_PRE range: 1400-2160 s - T_PRE (s) = 0.048 * R_TMR - T_MAX (s) = 10 * T_PRE
SJ2: Cut to enable charge timer.
TS - External Thermistor
- Connect TS to 10k NTC thermistor in the battery pack. - Connect a 10k resistor to GND if TS is not used.
VDD is 1.8V generated internally
OUT is the power-path management output. It manages current supplied from the USB input to both the battery and system. Or supplies battery power to the system when USB is not connected. OUT supply w/ USB: V_USB - 0.3V OUT supply w/o USB: V_BAT - 0.05V
I2C ADDR: 0x55
SJ5 sets the operation of the power LED. To either: - Power OUT indicator - !PGOOD! indicator (Good IN supply) - Open (LED disconnected)
5V BOOST
OE HIGH = Disconnected OE LOW = Connected S LOW = D1 S HIGH = D2
MOTION SUBSYSTEM
AUDIO SUBSYSTEM
POWER SUBSYSTEM
SOM
EINK_SUBSYSTEM
SAM
USB2.0
HAPTIC MOTOR
ACTIVE COOLING
DIGITAL PERIPHERAL
PCIE M.2
CAMERA

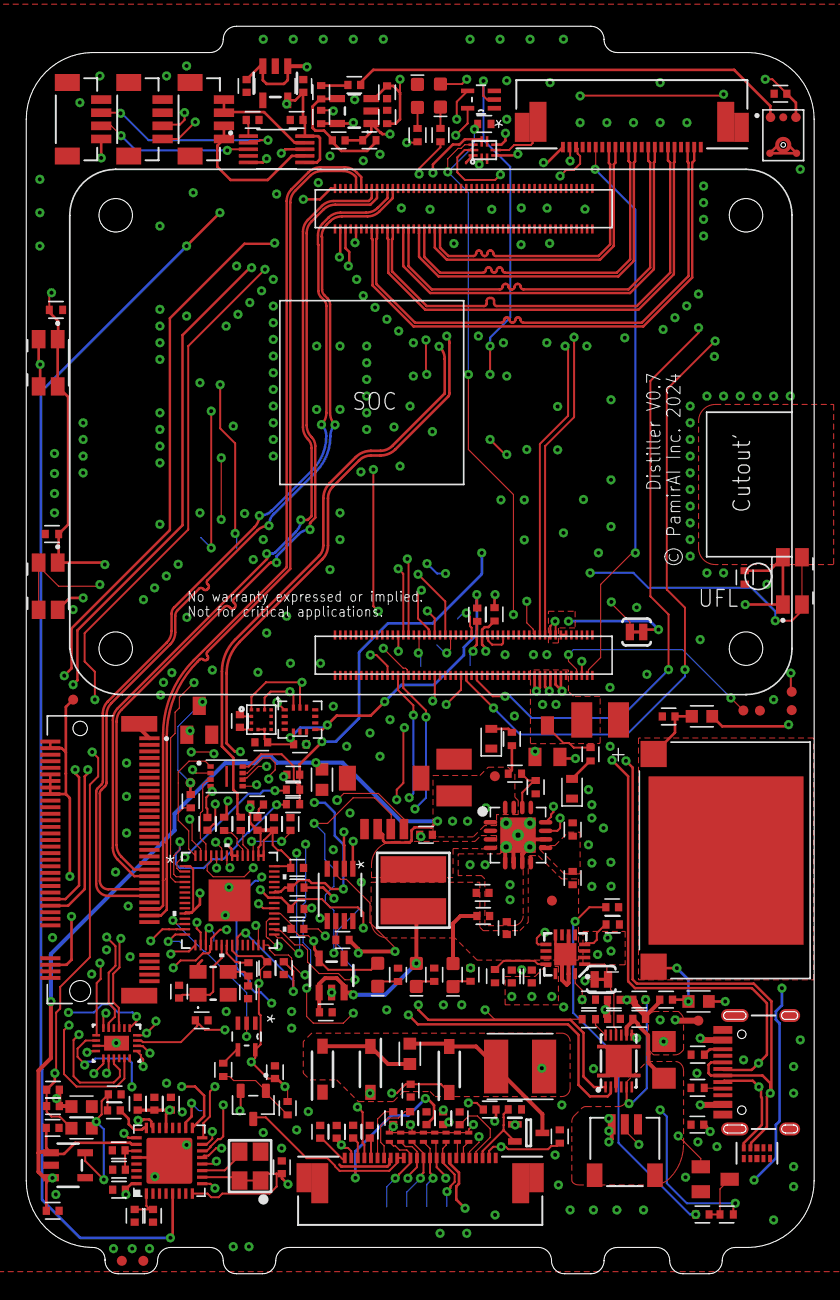
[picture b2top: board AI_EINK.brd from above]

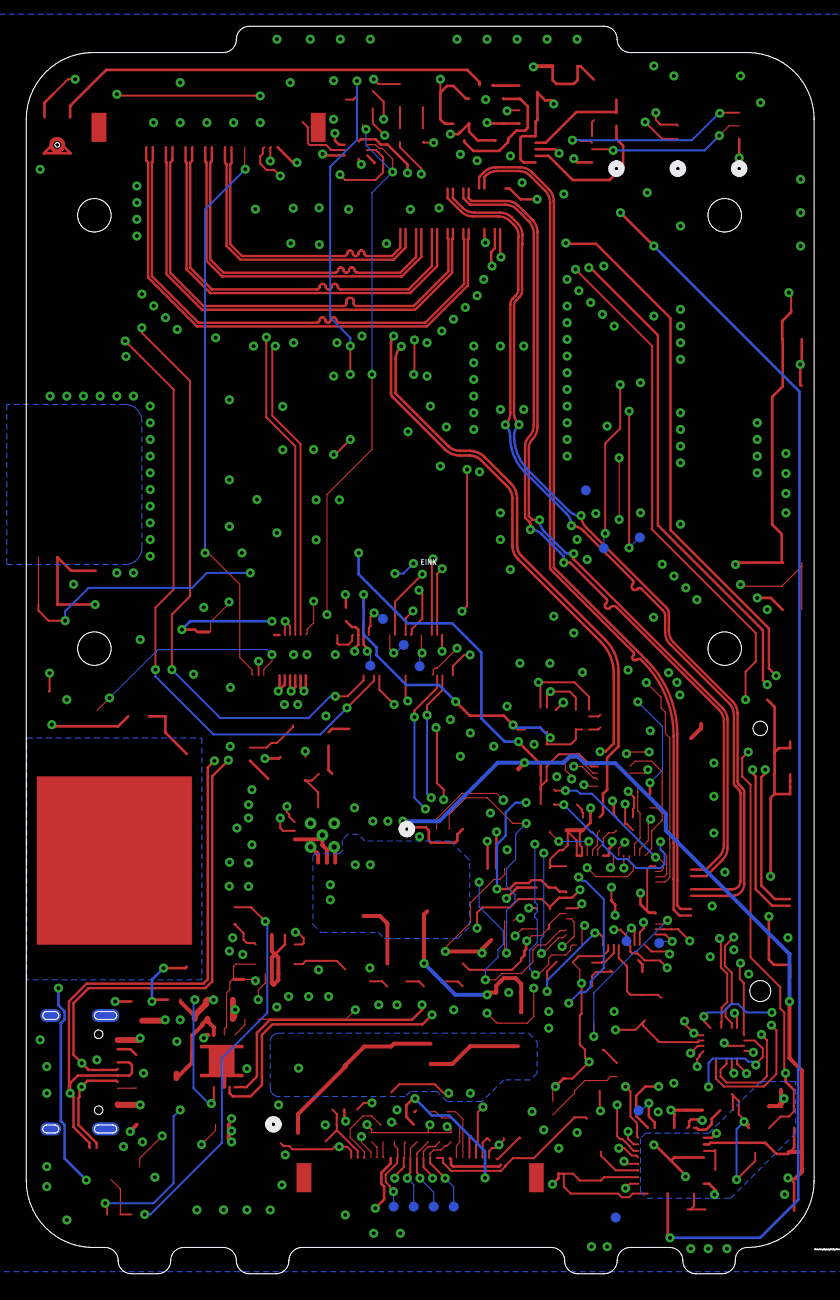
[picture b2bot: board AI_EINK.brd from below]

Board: 4 copper layers, 60.0 x 95.0 mm, 206 parts (15 on the bottom side), 150 nets.

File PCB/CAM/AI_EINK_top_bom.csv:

Comment,Designator,Footprint,LCSC Part #
0.01,J2 JP6 LEFTMIC RIGHTMIC S1 SJ1 SJ2 SJ3 SJ4 SJ5 SJ6 R12,1206,
0.1uF,C4 C16 C18,0805_10MGAP,
0.1uF,C25 C27 C47 C48 C49 C50 C51 C58,0603-NO,
0.47,R9,RESC1608X60,
0.47uF,C20,0603-CAP,
1.0uF,C19,0603-CAP,
1.0uF,C22,1206-CAP,
1.0uF,C30,0603-NO,
1.1k,R7 R21,0603-RES,
1.87M,R3,0805-NO,
1.87M (TPA2005D1DRBR),R1,_0805MP,
1K,R5 R20,0805-NO,
1K,R23,0603-RES,
1k,R8 R10 R28,R0603,
1nF,C36 C37 C38 C39 C40,0603,
1uF,C5 C8 C9 C10 C11 C12 C13 C14 C15,CAPC1608X85,
2.2uF,C2,0805-NO,
2.2uF+,C66,0805-NO,
4.7K,R15 R18,0603-RES,
4.7uF/50V,C17,0805_10MGAP,
5VBOOST,LED2,CHIPLED_0805_NOOUTLINE,
6.8uH,L1,INDUCTOR_5X5MM_TDK_VLC5045,
10K,R11,RESC1608X60,
10K,R14,0603-NO,
10K,R29 R33,0603-RES,
10uF,C1 C3 C7,0805-NO,
10uF,C21 C23,0805-CAP,
10uF,C24 C26 C31 C32 C33 C34 C35 C45 C46 C56 C57 C65,0805-NO,
24MHz 3.3V Oscillator,OSC1,OSC_3.2X2.5MM,
33pF,C52 C53 C54 C55,0603-NO,
100k,R24 R31,0603-RES,
100pF,C63 C64,0603-NO,
100uF,C6,C1210,
120o,FB9 FB10,0805-NO,
180,R22,0603-RES,
200K,R4 R13,0805-NO,
340K (RTT053403FTP),R2,_0805MP,
590,R6 R19,0603-RES,
524372471,J3,CON_524372471_MOL,
ACT (MHT192JGCT),D1,LED-0603@1,
ASPI-0403S-100M-T,L2,IND_ASPI-0403S-100M-T,
BLM18HE152SN1D,FL1 FL2,BEADC1608X95N,
BQ24075,U4,PVQFN-N16,
BQ27441DRZR-G1A,U3,PDSO-N12,
CHARGING FC-1608B1-470,D5,LED-0603,
CMS-18138A-SP,LS1,CUI_CMS-18138A-SP,
DF30FC-24DP-0.4V(81),OV5647,DF30FC-24DP,
DF40C-100DS-0.4V(51),RPI-CM1,RPI-CM4,
ECS-3225MV,OSC2,OSC_3.2X2.5MM,
FERRITE,FB4,0805-NO,
Ferrite,FB3,0805-NO,
MBR0530,D2 D3 D4,SOD3716X135N,
MC74VHC1G14DFT1G,U2,SOT65P210X110-5N,
MMUN2133LT1G,T1,SC59-BEC,
NFC_ANTENNA_25X15,ANT1,NFCANT_25X15,
PMIC,D6,LED-0603,
SI1308EDL-T1-GE3,Q1,SOT65P210X110-3N,
ST25DVXX_TSSOP,RF1,TSSOP8-4.4MM,
SYS_POW (19-213/Y2C-CQ2R2L/3T(CY)),LED3,LED-0603,
TEST-POINT3,GND GND13 GND22 GND25 GND26 GND27 RPIBOOT RPIBOOT1 RPIBOOT2 RPIBOOT3 RPIBOOT4 RPIBOOT5,PAD.03X.03,
TLV74315,U6,SOT23-5,
TLV74328,U5,SOT23-5,
TPS61090RSAR,U1,PVQFN-16,
WM8960,IC3,QFN32_5MM,
XL-2012VRC,LOW_BATT,CHIPLED_0805_NOOUTLINE,

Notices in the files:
PCB/AI_EINK.brd:
© PamirAI Inc. 2024
parts and their libraries:
microbuilder: This work is placed in the public domain, and may be freely used for commercial and non-commercial work with the following conditions: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
SparkFun-LED: Licensing: Creative Commons ShareAlike 4.0 International - https://creativecommons.org/licenses/by-sa/4.0
